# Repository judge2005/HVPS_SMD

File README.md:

# HVPS_SMD
A small, flexible nixie clock tube power supply. See the project description at [hackaday.io](https://hackaday.io/project/27899-nixie-tube-power-supply) for possibly more information than you thought you might ever need.

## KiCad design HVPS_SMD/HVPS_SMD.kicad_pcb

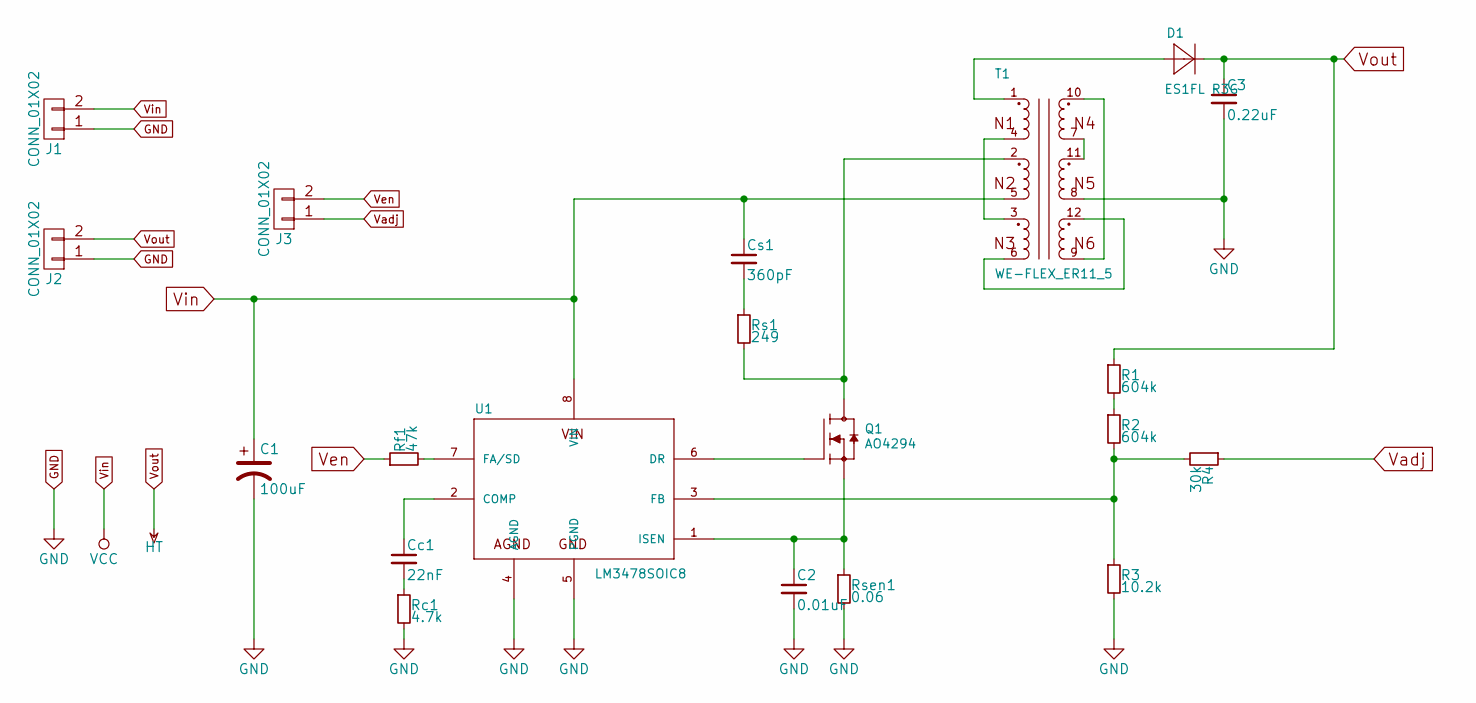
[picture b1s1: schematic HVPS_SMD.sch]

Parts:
C1: 100uF; C_1210
C2: 0.01uF; C_0603
C3: 0.22uF; C_1210
Cc1: 22nF; C_0603
Cs1: 360pF; C_0603
D1: ES1FL R3G; nixiemisc-DO-219AB
J1, J2, J3: CONN_01X02; SparkFun-Connectors-1X02_NO_SILK
Q1: AO4294; nixiemisc-SO08
R1, R2: 604k; R_0805
R3: 10.2k; R_0603
R4: 30k; R_0603
Rc1: 4.7k; R_0805
Rf1: 47k; R_0805
Rs1: 249; R_1206
Rsen1: 0.06; R_2010
T1: WE-FLEX_ER11_5; nixiemisc-WE-FLEX_ER11_5
U1: LM3478SOIC8; nixiemisc-SOIC8

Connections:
GND: C1.2, C2.2, C3.2, J1.1, J2.1, R3.2, Rc1.2, Rsen1.2, T1.8 (5), U1.4 (AGND), U1.5 (PGND)
unnamed: C2.1, Q1.1 (S), Q1.2 (S), Q1.3 (S), Rsen1.1, U1.1 (ISEN)
unnamed: Cc1.1, U1.2 (COMP)
unnamed: Cc1.2, Rc1.1
unnamed: Cs1.2, Rs1.1
unnamed: D1.A, T1.1
unnamed: Q1.4 (G), U1.6 (DR)
unnamed: Q1.5 (D), Q1.6 (D), Q1.7 (D), Q1.8 (D), Rs1.2, T1.2 (11)
unnamed: R1.2, R2.1
unnamed: R2.2, R3.1, R4.2, U1.3 (FB)
unnamed: Rf1.2, U1.7 (FA/SD)
unnamed: T1.3 (9), T1.4 (12)
unnamed: T1.9 (7), T1.10 (2)
unnamed: T1.7 (3), T1.11 (4)
unnamed: T1.6 (8), T1.12 (6)
Vadj: J3.1, R4.1
Ven: J3.2, Rf1.1
Vin: C1.1, Cs1.1, J1.2, T1.5 (10), U1.8 (VIN)
Vout: C3.1, D1.C, J2.2, R1.1

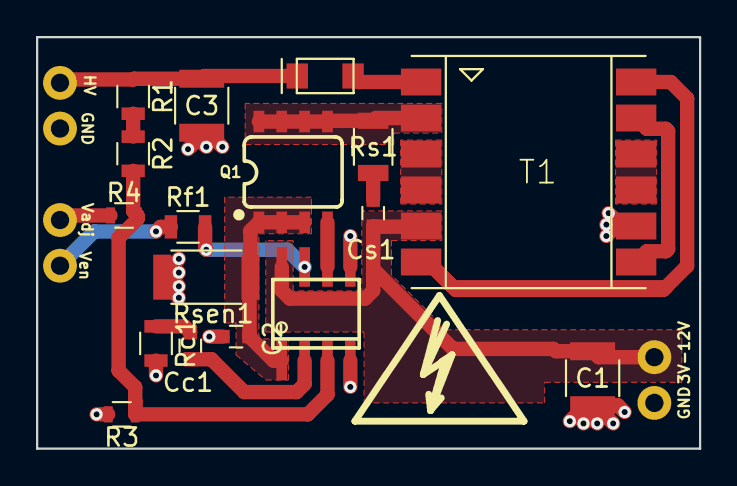
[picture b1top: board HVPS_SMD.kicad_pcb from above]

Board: 2 copper layers, 36.8 x 22.9 mm, 20 parts (0 on the bottom side), 19 nets.

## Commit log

2017-11-10 Updated readme with project link.
2017-11-10 added LTSpice model
2017-11-28 Fixed external footprint references
